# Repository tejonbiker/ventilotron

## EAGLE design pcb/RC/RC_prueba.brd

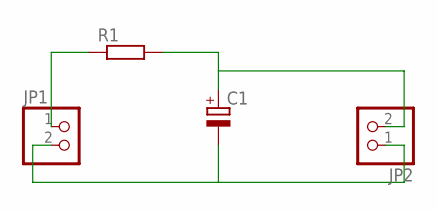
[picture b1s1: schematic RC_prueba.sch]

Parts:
C1: CPOL-EUA/3216-18R; A/3216-18R
JP1, JP2: PINHD-1X2; 1X02
R1: R-EU_MELF0204W; MINI_MELF-0204W

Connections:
unnamed: JP1.1, R1.1
unnamed: C1.+, JP2.2, R1.2
unnamed: C1.-, JP1.2, JP2.1

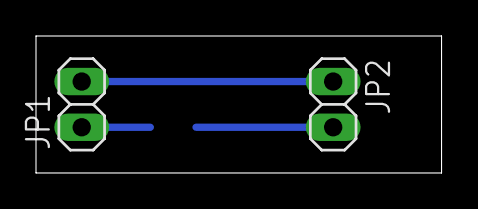
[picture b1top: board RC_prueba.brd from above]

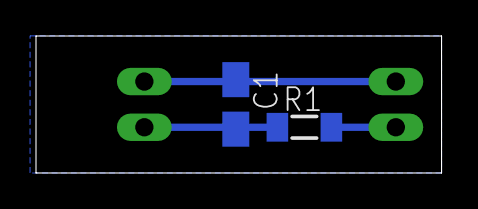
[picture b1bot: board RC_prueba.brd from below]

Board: 2 copper layers, 22.5 x 7.6 mm, 4 parts (2 on the bottom side), 3 nets.

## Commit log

2014-10-13 midi agregado
2014-10-13 agregue mi nombre
2014-10-13 respuesta al hola
2014-10-13 DAVID MODIFICO
2014-10-14 archivos eagle agregados
2014-10-16 something fixed
